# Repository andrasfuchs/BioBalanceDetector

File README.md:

Technically speaking Bio Balance Detector is a software and hardware combination (a data acquisition system - DAS) to detect, measure, display and analyze the electromagnetic energy field around living beings and indicate any potential health imbalance.  
  
These very weak, but measurable electromagnetic fields are the same what our doctors use while using an EEG (electroencephalogram) and ECG (electrocardiogram) devices. We use the information gathered there mainly to detect if we are sleeping, awake or alert, or if there is any problem with our heart's. My goal is to extend this phenomenon's measurements to our hands, or even our whole body.  
  
Technically I will need to connect an electromagnetic sensor matrix which is connected to a PC where the rendering would take place. It will look similar to a Wacom tablet, just like this:

Right now, with my [Mercury-16 prototype](https://github.com/andrasfuchs/BioBalanceDetector/wiki/Proto-%235---Mercury-16)  I reached a point where I have a working sensor matrix connected to a microcontroller. Every microcontroller is connected to 8 sensors and 1 emitter. The sensors detect electromagnetic fields, the emitters generate those fields. This part (1 microcontroller, 8 sensors, 1 emitter) is called the cell. These cells are daisy-chained and they all are connected to another microcontroller called the organizer. The cells digitize the analog signals (at 1kHz, 12bit) from the sensors (antennas) and forward them to the organizer. The organizer's job is to format the raw data and send it to the PC trough USB. The PC has a driver which further processes the data, and applies the filters if necessary. There are now WAV file writer, VTS file writer, FFT (Fast Fourier Transformation), averager and offsetter filters available. The driver is capable to work with [SciLab](http://www.scilab.org/) and [ParaView](https://www.paraview.org/), and it also has a very basic console application UI.  
  
You can browse the technical challenges I worked and I am working on on the [implementation wiki page](https://github.com/andrasfuchs/BioBalanceDetector/wiki/Implementation). Future plans include, but not limited to: fractal antenna design, analog low-pass Butterworth filters, Goertzel algorithm implementation on the cells, emitters, USB 3.0, Unity3D GUI and many more.  
  
I realize at this point that I need experienced, passionate people to more forward. I'm currently looking for people with the following expertise, so don't hesitate to contact me:  
* Hardware designer: PCB with [KiCad](https://www.kicad-pcb.org/), antenna and analog low pass filter design  
* Microcontroller firmware programmer: Atmel XMEGA programming with AVR C  
* PC driver developer: .NET, C#, signal processing and WebSockets  
* GUI: Unity3D, C# and WebSockets  
  
If you would like to get know the project more, check out the [wiki page](http://bit.ly/29OBsJ2) or contact me at <andras.fuchs@gmail.com>.

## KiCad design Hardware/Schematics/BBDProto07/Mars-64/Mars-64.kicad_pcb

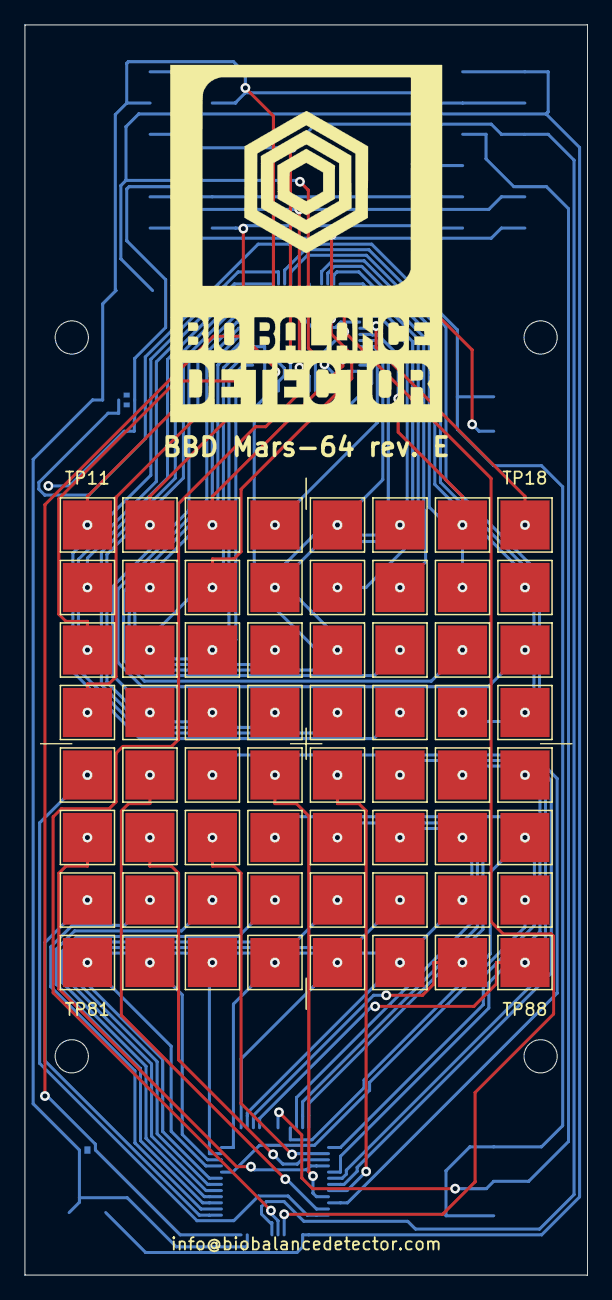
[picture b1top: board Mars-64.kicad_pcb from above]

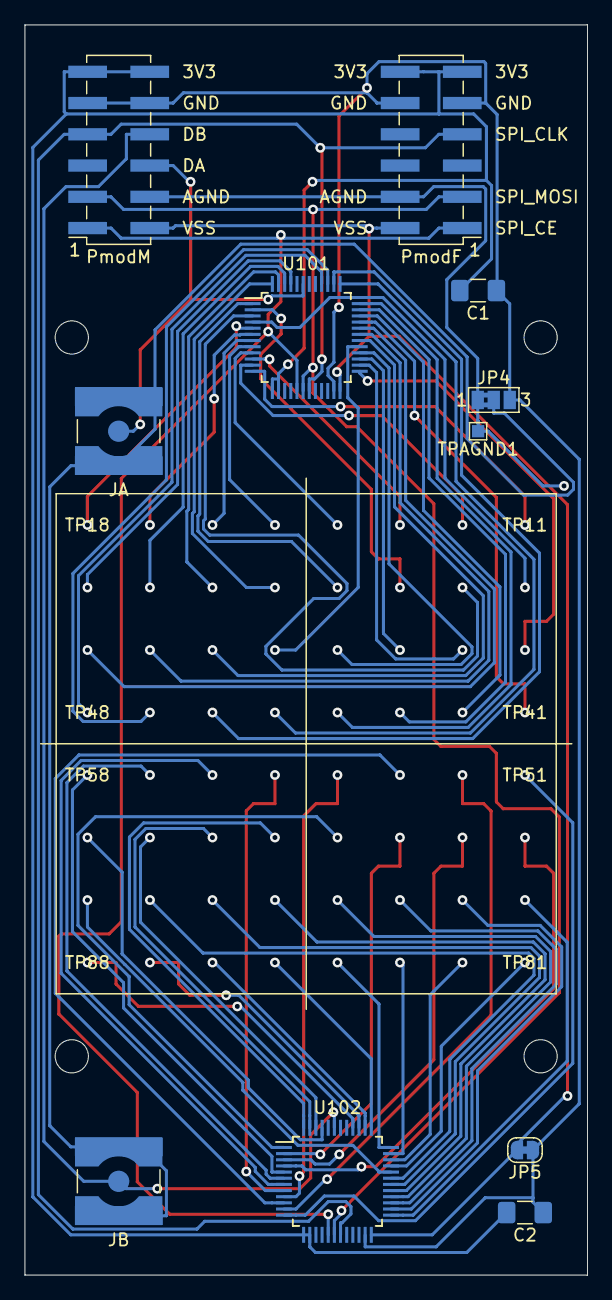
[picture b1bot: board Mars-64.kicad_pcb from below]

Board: 4 copper layers, 45.7 x 101.6 mm, 79 parts (11 on the bottom side), 74 nets.

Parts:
C1, C2: 100 nF; C_1206_3216Metric_Pad1.42x1.75mm_HandSolder
H1, H2, H3, H4: MountingHole; MountingHole_2.7mm_M2.5
JA: Conn_Coaxial; SMA_Amphenol_132134-10_Vertical
JB: Conn_Coaxial; SMA_Amphenol_132134-10_Vertical
JP4: Jumper_NC_Dual; SolderJumper-3_P1.3mm_Bridged2Bar12_Pad1.0x1.5mm_NumberLabe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
JP5: SolderJumper_2_Bridged; SolderJumper-2_P1.3mm_Bridged_RoundedPad1.0x1.5mm
PmodF: Conn_02x06_Top_Bottom; PinHeader_2x06_P2.54mm_Vertical_SMD_TopBottom
PmodM: Conn_02x06_Top_Bottom; PinHeader_2x06_P2.54mm_Vertical_SMD_TopBottom_Mirrored
TP101, TP102, TP103, TP104, TP105, TP106, TP107, TP108, TP109, TP110, TP111, TP112, TP113, TP114, TP115, TP116, TP117, TP118, TP119, TP120, TP121, TP122, TP123, TP124, TP125, TP126, TP127, TP128, TP129, TP130, TP131, TP132, TP201, TP202, TP203, TP204, TP205, TP206, TP207, TP208, TP209, TP210, TP211, TP212, TP213, TP214, TP215, TP216, TP217, TP218, TP219, TP220, TP221, TP222, TP223, TP224, TP225, TP226, TP227, TP228, TP229, TP230, TP231, TP232: TestPoint_Small; TestPoint_Pad_4.0x4.0mm
TPAGND1: TestPoint_Small; TestPoint_Pad_1.0x1.0mm
U101, U102: ADG731; TQFP-48_7x7mm_P0.5mm

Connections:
/AGND: JP4.1, PmodF.8, PmodM.8, TPAGND1.1
/DA: JA.1, PmodM.9, U101.43
/DB: JB.1, PmodM.10, U102.43
/SPI_CLK: PmodF.4, PmodM.4, U101.19, U102.19
/SPI_MOSI: PmodF.2, PmodM.2, U101.18, U102.18
/VCC3V3: C1.2, C2.2, PmodF.6, PmodF.12, PmodM.6, PmodM.12, U101.13, U101.14, U102.13, U102.14
/VSS: JP5.2, PmodF.7, PmodM.7, U101.24, U102.24
/~SPI_CE: PmodF.1, PmodM.1, U101.17, U102.17
GND: C1.1, C2.1, JP4.3, JP5.1, PmodF.5, PmodF.11, PmodM.5, PmodM.11, U101.23, U102.23
unnamed: JA.2, JB.2, JP4.2
unnamed: TP101.1, U101.12
unnamed: TP102.1, U101.11
unnamed: TP103.1, U101.10
unnamed: TP104.1, U101.9
unnamed: TP105.1, U101.8
unnamed: TP106.1, U101.7
unnamed: TP107.1, U101.6
unnamed: TP108.1, U101.5
unnamed: TP109.1, U101.4
unnamed: TP110.1, U101.3
unnamed: TP111.1, U101.2
unnamed: TP112.1, U101.1
unnamed: TP113.1, U101.48
unnamed: TP114.1, U101.47
unnamed: TP115.1, U101.46
unnamed: TP116.1, U101.45
unnamed: TP117.1, U101.25
unnamed: TP118.1, U101.26
unnamed: TP119.1, U101.27
unnamed: TP120.1, U101.28
unnamed: TP121.1, U101.29
unnamed: TP122.1, U101.30
unnamed: TP123.1, U101.31
unnamed: TP124.1, U101.32
unnamed: TP125.1, U101.33
unnamed: TP126.1, U101.34
unnamed: TP127.1, U101.35
unnamed: TP128.1, U101.36
unnamed: TP129.1, U101.37
unnamed: TP130.1, U101.38
unnamed: TP131.1, U101.39
unnamed: TP132.1, U101.40
unnamed: TP201.1, U102.12
unnamed: TP202.1, U102.11
unnamed: TP203.1, U102.10
unnamed: TP204.1, U102.9
unnamed: TP205.1, U102.8
unnamed: TP206.1, U102.7
unnamed: TP207.1, U102.6
unnamed: TP208.1, U102.5
unnamed: TP209.1, U102.4
unnamed: TP210.1, U102.3
unnamed: TP211.1, U102.2
unnamed: TP212.1, U102.1
unnamed: TP213.1, U102.48
unnamed: TP214.1, U102.47
unnamed: TP215.1, U102.46
unnamed: TP216.1, U102.45
unnamed: TP217.1, U102.25
unnamed: TP218.1, U102.26
unnamed: TP219.1, U102.27
unnamed: TP220.1, U102.28
unnamed: TP221.1, U102.29
unnamed: TP222.1, U102.30
unnamed: TP223.1, U102.31
unnamed: TP224.1, U102.32
unnamed: TP225.1, U102.33
unnamed: TP226.1, U102.34
unnamed: TP227.1, U102.35
unnamed: TP228.1, U102.36
unnamed: TP229.1, U102.37
unnamed: TP230.1, U102.38
unnamed: TP231.1, U102.39
unnamed: TP232.1, U102.40

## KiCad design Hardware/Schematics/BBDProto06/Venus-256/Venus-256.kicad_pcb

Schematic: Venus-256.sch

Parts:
JP101: VOUT1_JP; SolderJumper-2_P1.3mm_Bridged2Bar_Pad1.0x1.5mm
JP102: VOUT2_JP; SolderJumper-2_P1.3mm_Bridged2Bar_Pad1.0x1.5mm
TP101: VOUT3_TP; TestPoint_Pad_1.0x1.0mm
TP102: VOUT4_TP; TestPoint_Pad_1.0x1.0mm
U101: TPS22993; Texas_S-PWQFN-N20

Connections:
/CellMaster-01/VCC_MCU_P3V3: JP101.2; also elsewhere on the board
/CellMaster-02/VCC_MCU_P3V3: JP102.2; also elsewhere on the board
/RaspberryPiGPIOHeader/DC_POWER_3V3: U101.2, U101.4, U101.7, U101.8, U101.9, U101.10, U101.12, U101.14, U101.18; also elsewhere on the board
/RaspberryPiGPIOHeader/DC_POWER_5V0: U101.3; also elsewhere on the board
/RaspberryPiGPIOHeader/I2C_SCL1: U101.17; also elsewhere on the board
/RaspberryPiGPIOHeader/I2C_SDA1: U101.19; also elsewhere on the board
GND: U101.6, U101.13, U101.16, U101.20; also elsewhere on the board
unnamed: JP101.1, U101.5
unnamed: JP102.1, U101.1
unnamed: TP101.1, U101.15
unnamed: TP102.1, U101.11

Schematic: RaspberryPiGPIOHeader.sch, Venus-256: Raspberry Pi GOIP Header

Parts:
J201: RaspberryPi header; PinHeader_2x20_P2.54mm_Horizontal

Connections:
/CellMaster-01/SPI0_MISO: J201.21; also elsewhere on the board
/CellMaster-01/SPI0_MOSI: J201.19; also elsewhere on the board
/CellMaster-01/SPI0_SPCK: J201.23; also elsewhere on the board
/RaspberryPiGPIOHeader/DC_POWER_3V3: J201.1, J201.17; also elsewhere on the board
/RaspberryPiGPIOHeader/DC_POWER_5V0: J201.2, J201.4; also elsewhere on the board
/RaspberryPiGPIOHeader/I2C_SCL1: J201.5; also elsewhere on the board
/RaspberryPiGPIOHeader/I2C_SDA1: J201.3; also elsewhere on the board
GND: J201.6, J201.9, J201.14, J201.20, J201.25, J201.30, J201.34, J201.39; also elsewhere on the board

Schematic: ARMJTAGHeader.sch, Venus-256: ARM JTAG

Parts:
J301: ARM JTAG; PinHeader_2x10_P2.54mm_Horizontal
R301, R302, R303, R304: 0R; R_0603_1608Metric_Pad0.84x1.00mm_HandSolder

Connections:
/ARMJTAGHeader/SWCLK: R301.1; also elsewhere on the board
/ARMJTAGHeader/SWDIO: R303.2; also elsewhere on the board
/ARMJTAGHeader/TARGET_RESET: R302.1; also elsewhere on the board
/ARMJTAGHeader/TRACESWO: R304.2; also elsewhere on the board
/RaspberryPiGPIOHeader/DC_POWER_3V3: J301.1, J301.2; also elsewhere on the board
GND: J301.4, J301.6, J301.8, J301.10, J301.12, J301.14, J301.16, J301.18, J301.20; also elsewhere on the board
unnamed: J301.7, R303.1
unnamed: J301.9, R301.2
unnamed: J301.13, R304.1
unnamed: J301.15, R302.2

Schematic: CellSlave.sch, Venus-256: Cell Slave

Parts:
C401, C405, C407, C409, C411, C413, C416: 10uF; C_0603_1608Metric_Pad0.84x1.00mm_HandSolder
C402, C406, C408, C410, C412, C414, C415: 0.1uF; C_0603_1608Metric_Pad0.84x1.00mm_HandSolder
C403: 0.1uF,X8R; C_0603_1608Metric_Pad0.84x1.00mm_HandSolder
C404: 10uF,X5R; C_0603_1608Metric_Pad0.84x1.00mm_HandSolder
TP401: S01; TestPoint_Pad_1.0x1.0mm
TP402: S02; TestPoint_Pad_1.0x1.0mm
TP403: S03; TestPoint_Pad_1.0x1.0mm
TP404: S04; TestPoint_Pad_1.0x1.0mm
TP405: S05; TestPoint_Pad_1.0x1.0mm
TP406: S06; TestPoint_Pad_1.0x1.0mm
TP407: S07; TestPoint_Pad_1.0x1.0mm
TP408: S08; TestPoint_Pad_1.0x1.0mm
TP409: S09; TestPoint_Pad_1.0x1.0mm
TP410: S10; TestPoint_Pad_1.0x1.0mm
TP411: S11; TestPoint_Pad_1.0x1.0mm
TP412: S12; TestPoint_Pad_1.0x1.0mm
TP413: S13; TestPoint_Pad_1.0x1.0mm
TP414: S14; TestPoint_Pad_1.0x1.0mm
TP415: S15; TestPoint_Pad_1.0x1.0mm
TP416: S16; TestPoint_Pad_1.0x1.0mm
TP417: ADC_REF_OUT; TestPoint_Pad_1.0x1.0mm
U401: AD7616; LQFP-80_14x14mm_P0.65mm

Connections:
/CellMaster-01/ADC_BUSY0: U401.67; also elsewhere on the board
/CellMaster-01/ADC_CONVST0: U401.68; also elsewhere on the board
/CellMaster-01/ADC_RESET: U401.36; also elsewhere on the board
/CellMaster-01/DAC0: U401.1, U401.3, U401.8, U401.10, U401.11, U401.13, U401.18, U401.20, U401.21, U401.23, U401.25, U401.27, U401.74, U401.76, U401.78, U401.80; also elsewhere on the board
/CellMaster-01/SPI1_NPCS0: U401.63; also elsewhere on the board
/CellSlave-01A/SCLK: U401.55, U401.62; also elsewhere on the board
/CellSlave-01A/SDOA: U401.57; also elsewhere on the board
/RaspberryPiGPIOHeader/DC_POWER_3V3: C413.2, C414.2, U401.35, U401.40, U401.49; also elsewhere on the board
/RaspberryPiGPIOHeader/DC_POWER_5V0: C405.2, C406.1, C407.2, C408.2, C409.2, C410.2, C411.2, C412.2, U401.6, U401.15, U401.30, U401.71; also elsewhere on the board
GND: C401.2, C402.2, C403.2, C404.2, C405.1, C406.2, C407.1, C408.1, C409.1, C410.1, C411.1, C412.1, C413.1, C414.1, C415.2, C416.2, U401.5, U401.16, U401.29, U401.32, U401.34, U401.37, U401.38, U401.39, U401.41, U401.42, U401.43, U401.44, U401.45, U401.46, U401.47, U401.48, U401.50, U401.51, U401.53, U401.54, U401.58, U401.59, U401.60, U401.61, U401.64, U401.65, U401.66, U401.69, U401.72; also elsewhere on the board
unnamed: C401.1, C402.1, U401.70
unnamed: C403.1, TP417.1, U401.33
unnamed: C404.1, U401.31
unnamed: C415.1, C416.1, U401.52
unnamed: TP401.1, U401.73
unnamed: TP402.1, U401.75
unnamed: TP403.1, U401.77
unnamed: TP404.1, U401.79
unnamed: TP405.1, U401.9
unnamed: TP406.1, U401.7
unnamed: TP407.1, U401.4
unnamed: TP408.1, U401.2
unnamed: TP409.1, U401.19
unnamed: TP410.1, U401.17
unnamed: TP411.1, U401.14
unnamed: TP412.1, U401.12
unnamed: TP413.1, U401.28
unnamed: TP414.1, U401.26
unnamed: TP415.1, U401.24
unnamed: TP416.1, U401.22

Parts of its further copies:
C601, C605, C607, C609, C611, C613, C616, C701, C705, C707, C709, C711, C713, C716, C801, C805, C807, C809, C811, C813, C816, C1001, C1005, C1007, C1009, C1011, C1013, C1016: 10uF; C_0603_1608Metric_Pad0.84x1.00mm_HandSolder
C602, C606, C608, C610, C612, C614, C615, C702, C706, C708, C710, C712, C714, C715, C802, C806, C808, C810, C812, C814, C815, C1002, C1006, C1008, C1010, C1012, C1014, C1015: 0.1uF; C_0603_1608Metric_Pad0.84x1.00mm_HandSolder
C603, C703, C803, C1003: 0.1uF,X8R; C_0603_1608Metric_Pad0.84x1.00mm_HandSolder
C604, C704, C804, C1004: 10uF,X5R; C_0603_1608Metric_Pad0.84x1.00mm_HandSolder
TP601, TP701, TP801, TP1001: S01; TestPoint_Pad_1.0x1.0mm
TP602, TP702, TP802, TP1002: S02; TestPoint_Pad_1.0x1.0mm
TP603, TP703, TP803, TP1003: S03; TestPoint_Pad_1.0x1.0mm
TP604, TP704, TP804, TP1004: S04; TestPoint_Pad_1.0x1.0mm
TP605, TP705, TP805, TP1005: S05; TestPoint_Pad_1.0x1.0mm
TP606, TP706, TP806, TP1006: S06; TestPoint_Pad_1.0x1.0mm
TP607, TP707, TP807, TP1007: S07; TestPoint_Pad_1.0x1.0mm
TP608, TP708, TP808, TP1008: S08; TestPoint_Pad_1.0x1.0mm
TP609, TP709, TP809, TP1009: S09; TestPoint_Pad_1.0x1.0mm
TP610, TP710, TP810, TP1010: S10; TestPoint_Pad_1.0x1.0mm
TP611, TP711, TP811, TP1011: S11; TestPoint_Pad_1.0x1.0mm
TP612, TP712, TP812, TP1012: S12; TestPoint_Pad_1.0x1.0mm
TP613, TP713, TP813, TP1013: S13; TestPoint_Pad_1.0x1.0mm
TP614, TP714, TP814, TP1014: S14; TestPoint_Pad_1.0x1.0mm
TP615, TP715, TP815, TP1015: S15; TestPoint_Pad_1.0x1.0mm
TP616, TP716, TP816, TP1016: S16; TestPoint_Pad_1.0x1.0mm
TP617, TP717, TP817, TP1017: ADC_REF_OUT; TestPoint_Pad_1.0x1.0mm
U601, U701, U801, U1001: AD7616; LQFP-80_14x14mm_P0.65mm

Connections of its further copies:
/CellMaster-01/ADC_BUSY1: U601.67; also elsewhere on the board
/CellMaster-01/ADC_BUSY2: U701.67; also elsewhere on the board
/CellMaster-01/ADC_BUSY3: U801.67; also elsewhere on the board
/CellMaster-01/ADC_CONVST1: U601.68; also elsewhere on the board
/CellMaster-01/ADC_CONVST2: U701.68; also elsewhere on the board
/CellMaster-01/ADC_CONVST3: U801.68; also elsewhere on the board
/CellMaster-01/ADC_RESET: U601.36, U701.36, U801.36; also elsewhere on the board
/CellMaster-01/DAC0: U601.1, U601.3, U601.8, U601.10, U601.11, U601.13, U601.18, U601.20, U601.21, U601.23, U601.25, U601.27, U601.74, U601.76, U601.78, U601.80, U701.1, U701.3, U701.8, U701.10, U701.11, U701.13, U701.18, U701.20, U701.21, U701.23, U701.25, U701.27, U701.74, U701.76, U701.78, U701.80, U801.1, U801.3, U801.8, U801.10, U801.11, U801.13, U801.18, U801.20, U801.21, U801.23, U801.25, U801.27, U801.74, U801.76, U801.78, U801.80; also elsewhere on the board
/CellMaster-01/SPI1_NPCS1: U601.63; also elsewhere on the board
/CellMaster-01/SPI1_NPCS2: U701.63; also elsewhere on the board
/CellMaster-01/SPI1_NPCS3: U801.63; also elsewhere on the board
/CellMaster-02/ADC_BUSY0: U1001.67; also elsewhere on the board
/CellMaster-02/ADC_CONVST0: U1001.68; also elsewhere on the board
/CellMaster-02/ADC_RESET: U1001.36; also elsewhere on the board
/CellMaster-02/DAC0: U1001.1, U1001.3, U1001.8, U1001.10, U1001.11, U1001.13, U1001.18, U1001.20, U1001.21, U1001.23, U1001.25, U1001.27, U1001.74, U1001.76, U1001.78, U1001.80; also elsewhere on the board
/CellMaster-02/SPI1_NPCS0: U1001.63; also elsewhere on the board
/CellSlave-01A/SCLK: U601.55, U601.62, U701.55, U701.62, U801.55, U801.62; also elsewhere on the board
/CellSlave-01A/SDOA: U601.57, U701.57, U801.57; also elsewhere on the board
/CellSlave-02A/SCLK: U1001.62; also elsewhere on the board
/CellSlave-02A/SDI: U1001.55; also elsewhere on the board
/CellSlave-02A/SDOA: U1001.57; also elsewhere on the board
/RaspberryPiGPIOHeader/DC_POWER_3V3: C613.2, C614.2, C713.2, C714.2, C813.2, C814.2, C1013.2, C1014.2, U601.35, U601.40, U601.49, U701.35, U701.40, U701.49, U801.35, U801.40, U801.49, U1001.35, U1001.40, U1001.49; also elsewhere on the board
/RaspberryPiGPIOHeader/DC_POWER_5V0: C605.2, C606.1, C607.2, C608.2, C609.2, C610.2, C611.2, C612.2, C705.2, C706.1, C707.2, C708.2, C709.2, C710.2, C711.2, C712.2, C805.2, C806.1, C807.2, C808.2, C809.2, C810.2, C811.2, C812.2, C1005.2, C1006.1, C1007.2, C1008.2, C1009.2, C1010.2, C1011.2, C1012.2, U601.6, U601.15, U601.30, U601.71, U701.6, U701.15, U701.30, U701.71, U801.6, U801.15, U801.30, U801.71, U1001.6, U1001.15, U1001.30, U1001.71; also elsewhere on the board
GND: C601.2, C602.2, C603.2, C604.2, C605.1, C606.2, C607.1, C608.1, C609.1, C610.1, C611.1, C612.1, C613.1, C614.1, C615.2, C616.2, C701.2, C702.2, C703.2, C704.2, C705.1, C706.2, C707.1, C708.1, C709.1, C710.1, C711.1, C712.1, C713.1, C714.1, C715.2, C716.2, C801.2, C802.2, C803.2, C804.2, C805.1, C806.2, C807.1, C808.1, C809.1, C810.1, C811.1, C812.1, C813.1, C814.1, C815.2, C816.2, C1001.2, C1002.2, C1003.2, C1004.2, C1005.1, C1006.2, C1007.1, C1008.1, C1009.1, C1010.1, C1011.1, C1012.1, C1013.1, C1014.1, C1015.2, C1016.2, U601.5, U601.16, U601.29, U601.32, U601.34, U601.37, U601.38, U601.39, U601.41, U601.42, U601.43, U601.44, U601.45, U601.46, U601.47, U601.48, U601.50, U601.51, U601.53, U601.54, U601.58, U601.59, U601.60, U601.61, U601.64, U601.65, U601.66, U601.69, U601.72, U701.5, U701.16, U701.29, U701.32, U701.34, U701.37, U701.38, U701.39, U701.41, U701.42, U701.43, U701.44, U701.45, U701.46, U701.47, U701.48, U701.50, U701.51, U701.53, U701.54, U701.58, U701.59, U701.60, U701.61, U701.64, U701.65, U701.66, U701.69, U701.72, U801.5, U801.16, U801.29, U801.32, U801.34, U801.37, U801.38, U801.39, U801.41, U801.42, U801.43, U801.44, U801.45, U801.46, U801.47, U801.48, U801.50, U801.51, U801.53, U801.54, U801.58, U801.59, U801.60, U801.61, U801.64, U801.65, U801.66, U801.69, U801.72, U1001.5, U1001.16, U1001.29, U1001.32, U1001.34, U1001.37, U1001.38, U1001.39, U1001.41, U1001.42, U1001.43, U1001.44, U1001.45, U1001.46, U1001.47, U1001.48, U1001.50, U1001.51, U1001.53, U1001.54, U1001.58, U1001.59, U1001.60, U1001.61, U1001.64, U1001.65, U1001.66, U1001.69, U1001.72; also elsewhere on the board
unnamed: C601.1, C602.1, U601.70
unnamed: C603.1, TP617.1, U601.33
unnamed: C604.1, U601.31
unnamed: C615.1, C616.1, U601.52
unnamed: C701.1, C702.1, U701.70
unnamed: C703.1, TP717.1, U701.33
unnamed: C704.1, U701.31
unnamed: C715.1, C716.1, U701.52
unnamed: C801.1, C802.1, U801.70
unnamed: C803.1, TP817.1, U801.33
unnamed: C804.1, U801.31
unnamed: C815.1, C816.1, U801.52
unnamed: C1001.1, C1002.1, U1001.70
unnamed: C1003.1, TP1017.1, U1001.33
unnamed: C1004.1, U1001.31
unnamed: C1015.1, C1016.1, U1001.52
unnamed: TP601.1, U601.73
unnamed: TP602.1, U601.75
unnamed: TP603.1, U601.77
unnamed: TP604.1, U601.79
unnamed: TP605.1, U601.9
unnamed: TP606.1, U601.7
unnamed: TP607.1, U601.4
unnamed: TP608.1, U601.2
unnamed: TP609.1, U601.19
unnamed: TP610.1, U601.17
unnamed: TP611.1, U601.14
unnamed: TP612.1, U601.12
unnamed: TP613.1, U601.28
unnamed: TP614.1, U601.26
unnamed: TP615.1, U601.24
unnamed: TP616.1, U601.22
unnamed: TP701.1, U701.73
unnamed: TP702.1, U701.75
unnamed: TP703.1, U701.77
unnamed: TP704.1, U701.79
unnamed: TP705.1, U701.9
unnamed: TP706.1, U701.7
unnamed: TP707.1, U701.4
unnamed: TP708.1, U701.2
unnamed: TP709.1, U701.19
unnamed: TP710.1, U701.17
unnamed: TP711.1, U701.14
unnamed: TP712.1, U701.12
unnamed: TP713.1, U701.28
unnamed: TP714.1, U701.26
unnamed: TP715.1, U701.24
unnamed: TP716.1, U701.22
unnamed: TP801.1, U801.73
unnamed: TP802.1, U801.75
unnamed: TP803.1, U801.77
unnamed: TP804.1, U801.79
unnamed: TP805.1, U801.9
unnamed: TP806.1, U801.7
unnamed: TP807.1, U801.4
unnamed: TP808.1, U801.2
unnamed: TP809.1, U801.19
unnamed: TP810.1, U801.17
unnamed: TP811.1, U801.14
unnamed: TP812.1, U801.12
unnamed: TP813.1, U801.28
unnamed: TP814.1, U801.26
unnamed: TP815.1, U801.24
unnamed: TP816.1, U801.22
unnamed: TP1001.1, U1001.73
unnamed: TP1002.1, U1001.75
unnamed: TP1003.1, U1001.77
unnamed: TP1004.1, U1001.79
unnamed: TP1005.1, U1001.9
unnamed: TP1006.1, U1001.7
unnamed: TP1007.1, U1001.4
unnamed: TP1008.1, U1001.2
unnamed: TP1009.1, U1001.19
unnamed: TP1010.1, U1001.17
unnamed: TP1011.1, U1001.14
unnamed: TP1012.1, U1001.12
unnamed: TP1013.1, U1001.28
unnamed: TP1014.1, U1001.26
unnamed: TP1015.1, U1001.24
unnamed: TP1016.1, U1001.22

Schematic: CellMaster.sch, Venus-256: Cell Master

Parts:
C501: 10uF; C_0603_1608Metric_Pad0.84x1.00mm_HandSolder
C502, C503, C504, C506, C507, C508, C509, C510, C511, C512, C513, C514, C515, C516: 100nF; C_0603_1608Metric_Pad0.84x1.00mm_HandSolder
C505: 10pF; C_0603_1608Metric_Pad0.84x1.00mm_HandSolder
D501: LED_ARGB; LED_RGB_1210
JP501: GPAD_JP; SolderJumper-3_P1.3mm_Open_Pad1.0x1.5mm
L501: L; L_0603_1608Metric_Pad0.84x1.00mm_HandSolder
R501: 5.62K; R_0603_1608Metric_Pad0.84x1.00mm_HandSolder
TP501: AFE0_AD0; TestPoint_Pad_1.0x1.0mm
TP502: AFE0_AD1; TestPoint_Pad_1.0x1.0mm
TP503: ADVREF; TestPoint_Pad_1.0x1.0mm
TP504: GPAD; TestPoint_Pad_1.0x1.0mm
U501: ATSAME70Q21A-AN; LQFP-144_20x20mm_P0.5mm

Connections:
/ARMJTAGHeader/SWCLK: U501.89 (PB7/SWCLK/TCK); also elsewhere on the board
/ARMJTAGHeader/SWDIO: U501.79 (PB6/SWDIO/TMS); also elsewhere on the board
/ARMJTAGHeader/TARGET_RESET: U501.83 (NRST); also elsewhere on the board
/ARMJTAGHeader/TRACESWO: U501.109 (PB5/TDO/TRACESWO/WKUP13); also elsewhere on the board
/CellMaster-01/ADC_BUSY0: U501.46 (PA23); also elsewhere on the board
/CellMaster-01/ADC_BUSY1: U501.56 (PA24); also elsewhere on the board
/CellMaster-01/ADC_BUSY2: U501.59 (PA25); also elsewhere on the board
/CellMaster-01/ADC_BUSY3: U501.62 (PA26); also elsewhere on the board
/CellMaster-01/ADC_CONVST0: U501.4 (PE0/AFE1_AD11); also elsewhere on the board
/CellMaster-01/ADC_CONVST1: U501.6 (PE1); also elsewhere on the board
/CellMaster-01/ADC_CONVST2: U501.7 (PE2); also elsewhere on the board
/CellMaster-01/ADC_CONVST3: U501.10 (PE3/AFE1_AD10); also elsewhere on the board
/CellMaster-01/ADC_RESET: U501.70 (PA27); also elsewhere on the board
/CellMaster-01/DAC0: U501.20 (PB1/AFE1_AD0/RTCOUT1), U501.144 (PB13/DAC0); also elsewhere on the board
/CellMaster-01/SPI0_MISO: U501.65 (SPI0_MISO/PD20); also elsewhere on the board
/CellMaster-01/SPI0_MOSI: U501.63 (SPI0_MOSI/PD21); also elsewhere on the board
/CellMaster-01/SPI0_SPCK: U501.60 (SPI0_SPCK/PD22); also elsewhere on the board
/CellMaster-01/SPI1_NPCS0: U501.133 (SPI1_NPCS0/PC25); also elsewhere on the board
/CellMaster-01/SPI1_NPCS1: U501.76 (SPI1_NPCS1/PC28); also elsewhere on the board
/CellMaster-01/SPI1_NPCS2: U501.16 (SPI1_NPCS2/AFE1_AD4/PC29); also elsewhere on the board
/CellMaster-01/SPI1_NPCS3: U501.15 (SPI1_NPCS3/AFE1_AD5/PC30); also elsewhere on the board
/CellMaster-01/VCC_MCU_P3V3: C501.1, C503.1, C504.1, C506.1, C507.1, C508.1, C509.1, C510.1, C511.1, C512.1, C513.1, C514.1, C515.1, C516.1, L501.2, U501.5 (VDDIN), U501.29 (VDDCORE), U501.30 (VDDIO), U501.33 (VDDCORE), U501.43 (VDDIO), U501.50 (VDDCORE), U501.72 (VDDIO), U501.80 (VDDIO), U501.81 (VDDCORE), U501.96 (VDDIO), U501.107 (VDDCORE), U501.134 (VDDUTMII), U501.143 (VDDPLLUSB); also elsewhere on the board
/CellSlave-01A/SCLK: U501.12 (SPI1_MOSI/AFE1_AD8/PC27), U501.130 (SPI1_SPCK/PC24); also elsewhere on the board
/CellSlave-01A/SDOA: U501.13 (SPI1_MISO/AFE1_AD7/PC26); also elsewhere on the board
GND: C501.2, C502.2, C503.2, C504.2, C505.2, C506.2, C507.2, C508.2, C509.2, C510.2, C511.2, C512.2, C513.2, C514.2, C515.2, C516.2, JP501.3, R501.2, U501.8 (VREFN), U501.44 (GND), U501.61 (GND), U501.95 (GND), U501.115 (GND), U501.135 (GND), U501.138 (GND); also elsewhere on the board
unnamed: C502.1, L501.1, TP503.1, U501.9 (VREFP)
unnamed: C505.1, R501.1, U501.140 (VBG)
unnamed: D501.1, U501.51 (PA14/WKUP8/PIODCEN1)
unnamed: D501.2, U501.42 (PA13/PIODC7)
unnamed: D501.3, U501.68 (PA12/PIODC6)
unnamed: D501.4, U501.64 (PA11/WKUP7/PIODC5)
unnamed: JP501.1, U501.1 (SPI1_NPCS1/DAC1/PD0)
unnamed: JP501.2, TP504.1
unnamed: TP501.1, U501.34 (UTXD3/AFE0_AD0/PD30)
unnamed: TP502.1, U501.32 (PA21/AFE0_AD1/PIODCEN2)

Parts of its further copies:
C901: 10uF; C_0603_1608Metric_Pad0.84x1.00mm_HandSolder
C902, C903, C904, C906, C907, C908, C909, C910, C911, C912, C913, C914, C915, C916: 100nF; C_0603_1608Metric_Pad0.84x1.00mm_HandSolder
C905: 10pF; C_0603_1608Metric_Pad0.84x1.00mm_HandSolder
D901: LED_ARGB; LED_RGB_1210
JP901: GPAD_JP; SolderJumper-3_P1.3mm_Open_Pad1.0x1.5mm
L901: L; L_0603_1608Metric_Pad0.84x1.00mm_HandSolder
R901: 5.62K; R_0603_1608Metric_Pad0.84x1.00mm_HandSolder
TP901: AFE0_AD0; TestPoint_Pad_1.0x1.0mm
TP902: AFE0_AD1; TestPoint_Pad_1.0x1.0mm
TP903: ADVREF; TestPoint_Pad_1.0x1.0mm
TP904: GPAD; TestPoint_Pad_1.0x1.0mm
U901: ATSAME70Q21A-AN; LQFP-144_20x20mm_P0.5mm

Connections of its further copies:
/ARMJTAGHeader/SWCLK: U901.89 (PB7/SWCLK/TCK); also elsewhere on the board
/ARMJTAGHeader/SWDIO: U901.79 (PB6/SWDIO/TMS); also elsewhere on the board
/ARMJTAGHeader/TARGET_RESET: U901.83 (NRST); also elsewhere on the board
/ARMJTAGHeader/TRACESWO: U901.109 (PB5/TDO/TRACESWO/WKUP13); also elsewhere on the board
/CellMaster-01/SPI0_MISO: U901.65 (SPI0_MISO/PD20); also elsewhere on the board
/CellMaster-01/SPI0_MOSI: U901.63 (SPI0_MOSI/PD21); also elsewhere on the board
/CellMaster-01/SPI0_SPCK: U901.60 (SPI0_SPCK/PD22); also elsewhere on the board
/CellMaster-02/ADC_BUSY0: U901.46 (PA23); also elsewhere on the board
/CellMaster-02/ADC_CONVST0: U901.4 (PE0/AFE1_AD11); also elsewhere on the board
/CellMaster-02/ADC_RESET: U901.70 (PA27); also elsewhere on the board
/CellMaster-02/DAC0: U901.20 (PB1/AFE1_AD0/RTCOUT1), U901.144 (PB13/DAC0); also elsewhere on the board
/CellMaster-02/SPI1_NPCS0: U901.133 (SPI1_NPCS0/PC25); also elsewhere on the board
/CellMaster-02/VCC_MCU_P3V3: C901.1, C903.1, C904.1, C906.1, C907.1, C908.1, C909.1, C910.1, C911.1, C912.1, C913.1, C914.1, C915.1, C916.1, L901.2, U901.5 (VDDIN), U901.29 (VDDCORE), U901.30 (VDDIO), U901.33 (VDDCORE), U901.43 (VDDIO), U901.50 (VDDCORE), U901.72 (VDDIO), U901.80 (VDDIO), U901.81 (VDDCORE), U901.96 (VDDIO), U901.107 (VDDCORE), U901.134 (VDDUTMII), U901.143 (VDDPLLUSB); also elsewhere on the board
/CellSlave-02A/SCLK: U901.130 (SPI1_SPCK/PC24); also elsewhere on the board
/CellSlave-02A/SDI: U901.12 (SPI1_MOSI/AFE1_AD8/PC27); also elsewhere on the board
/CellSlave-02A/SDOA: U901.13 (SPI1_MISO/AFE1_AD7/PC26); also elsewhere on the board
GND: C901.2, C902.2, C903.2, C904.2, C905.2, C906.2, C907.2, C908.2, C909.2, C910.2, C911.2, C912.2, C913.2, C914.2, C915.2, C916.2, JP901.3, R901.2, U901.8 (VREFN), U901.44 (GND), U901.61 (GND), U901.95 (GND), U901.115 (GND), U901.135 (GND), U901.138 (GND); also elsewhere on the board
unnamed: C902.1, L901.1, TP903.1, U901.9 (VREFP)
unnamed: C905.1, R901.1, U901.140 (VBG)
unnamed: D901.1, U901.51 (PA14/WKUP8/PIODCEN1)
unnamed: D901.2, U901.42 (PA13/PIODC7)
unnamed: D901.3, U901.68 (PA12/PIODC6)
unnamed: D901.4, U901.64 (PA11/WKUP7/PIODC5)
unnamed: JP901.1, U901.1 (SPI1_NPCS1/DAC1/PD0)
unnamed: JP901.2, TP904.1
unnamed: TP901.1, U901.34 (UTXD3/AFE0_AD0/PD30)
unnamed: TP902.1, U901.32 (PA21/AFE0_AD1/PIODCEN2)

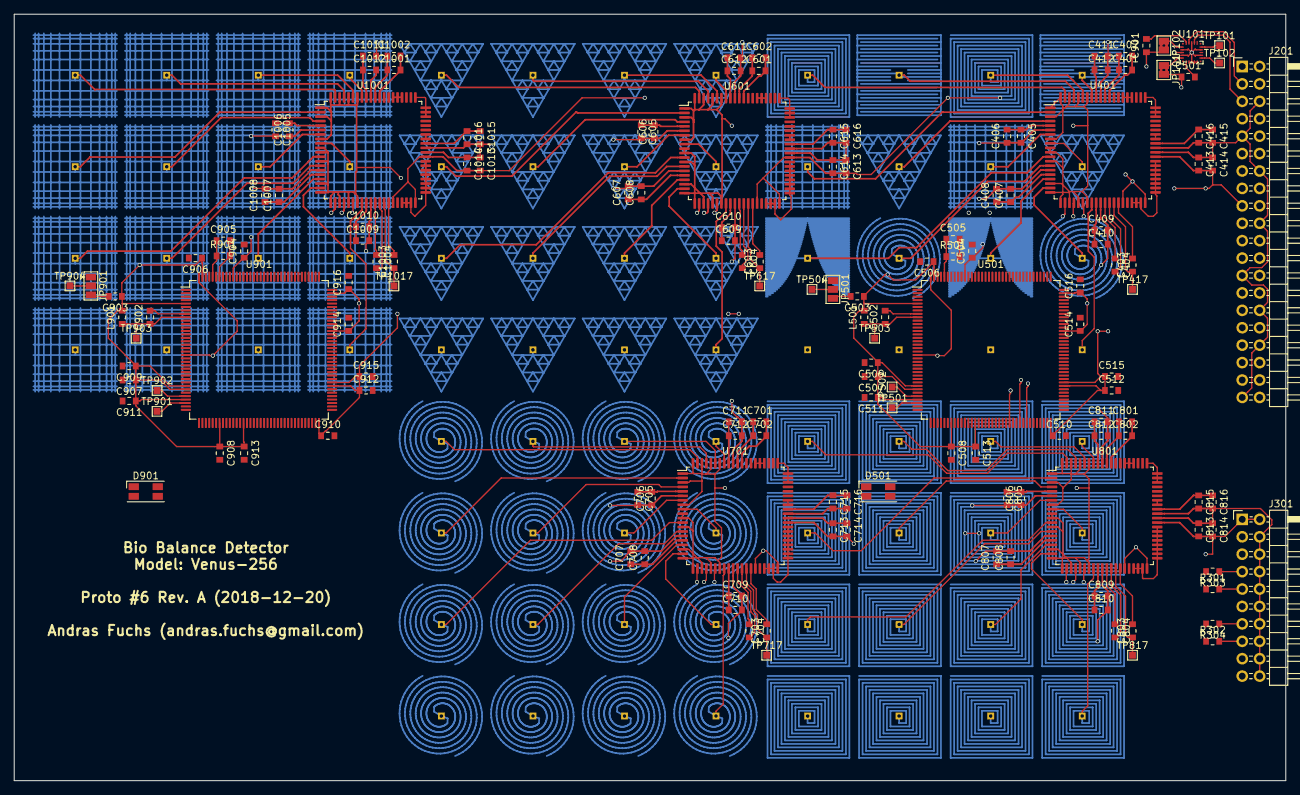
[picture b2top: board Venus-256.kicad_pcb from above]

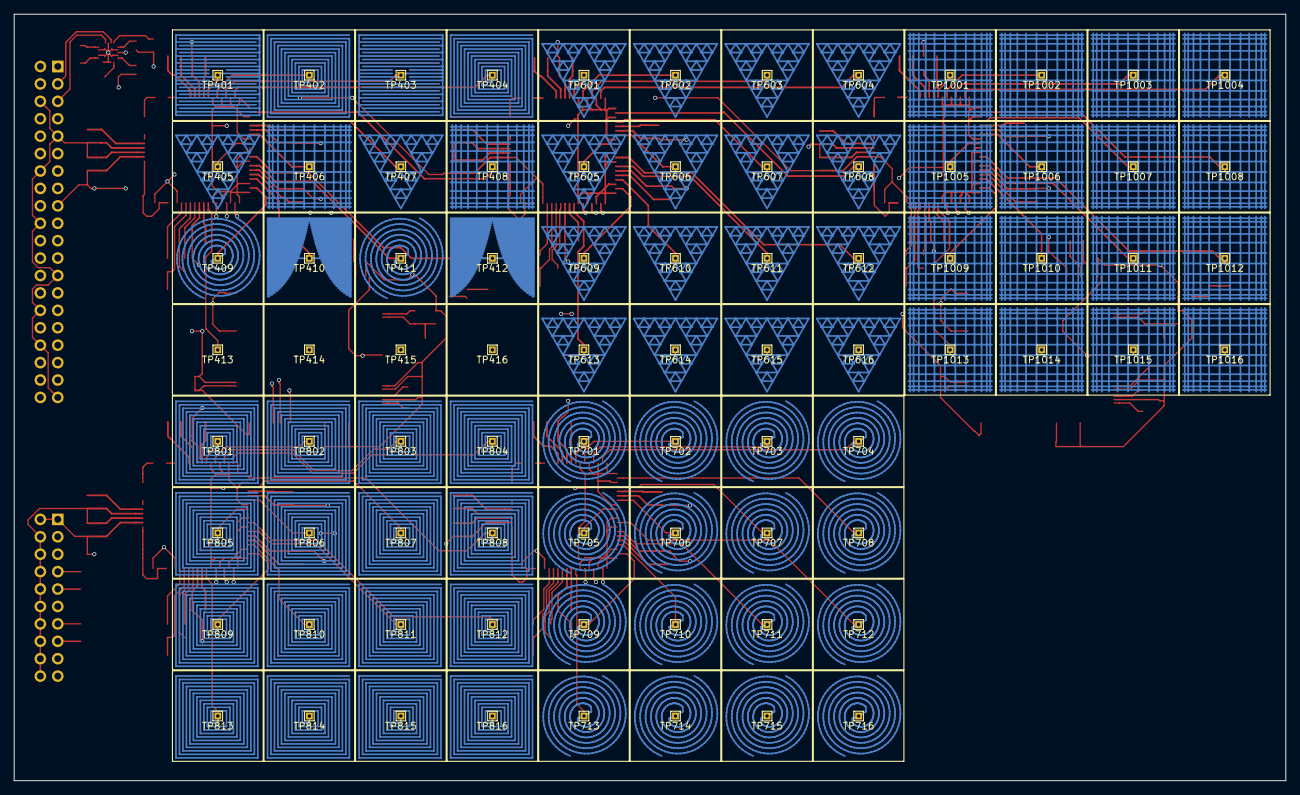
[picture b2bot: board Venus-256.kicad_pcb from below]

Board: 4 copper layers, 185.4 x 111.8 mm, 231 parts (80 on the bottom side), 166 nets.

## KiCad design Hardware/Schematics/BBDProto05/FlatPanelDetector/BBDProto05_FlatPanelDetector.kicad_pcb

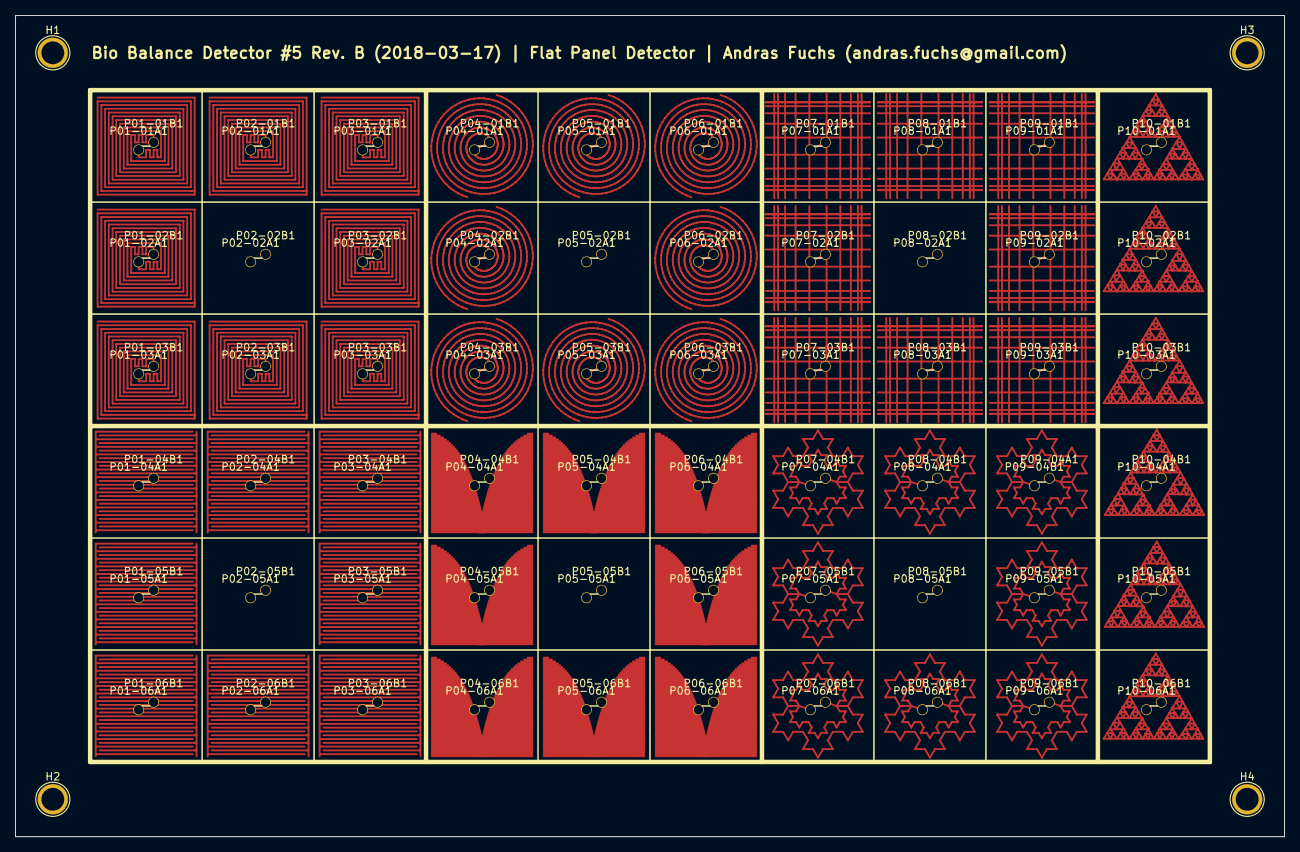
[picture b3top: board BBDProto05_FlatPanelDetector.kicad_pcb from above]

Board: 2 copper layers, 170.0 x 110.0 mm, 124 parts (0 on the bottom side), 60 nets.

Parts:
H1, H2, H3, H4: VIA_06MM; 1pin
P01-01A1, P01-01B1, P01-02A1, P01-02B1, P01-03A1, P01-03B1, P01-04A1, P01-04B1, P01-05A1, P01-05B1, P01-06A1, P01-06B1, P02-01A1, P02-01B1, P02-02A1, P02-02B1, P02-03A1, P02-03B1, P02-04A1, P02-04B1, P02-05A1, P02-05B1, P02-06A1, P02-06B1, P03-01A1, P03-01B1, P03-02A1, P03-02B1, P03-03A1, P03-03B1, P03-04A1, P03-04B1, P03-05A1, P03-05B1, P03-06A1, P03-06B1, P04-01A1, P04-01B1, P04-02A1, P04-02B1, P04-03A1, P04-03B1, P04-04A1, P04-04B1, P04-05A1, P04-05B1, P04-06A1, P04-06B1, P05-01A1, P05-01B1, P05-02A1, P05-02B1, P05-03A1, P05-03B1, P05-04A1, P05-04B1, P05-05A1, P05-05B1, P05-06A1, P05-06B1, P06-01A1, P06-01B1, P06-02A1, P06-02B1, P06-03A1, P06-03B1, P06-04A1, P06-04B1, P06-05A1, P06-05B1, P06-06A1, P06-06B1, P07-01A1, P07-01B1, P07-02A1, P07-02B1, P07-03A1, P07-03B1, P07-04A1, P07-04B1, P07-05A1, P07-05B1, P07-06A1, P07-06B1, P08-01A1, P08-01B1, P08-02A1, P08-02B1, P08-03A1, P08-03B1, P08-04A1, P08-04B1, P08-05A1, P08-05B1, P08-06A1, P08-06B1, P09-01A1, P09-01B1, P09-02A1, P09-02B1, P09-03A1, P09-03B1, P09-04A1, P09-04B1, P09-05A1, P09-05B1, P09-06A1, P09-06B1, P10-01A1, P10-01B1, P10-02A1, P10-02B1, P10-03A1, P10-03B1, P10-04A1, P10-04B1, P10-05A1, P10-05B1, P10-06A1, P10-06B1: VIA_06MM; SolderWirePad_single_0-4mmDrill

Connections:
unnamed: P01-01A1.1, P01-01B1.1
unnamed: P01-02A1.e1, P01-02B1.1
unnamed: P01-03A1.1, P01-03B1.1
unnamed: P01-04A1.1, P01-04B1.1
unnamed: P01-05A1.1, P01-05B1.1
unnamed: P01-06A1.1, P01-06B1.1
unnamed: P02-01A1.1, P02-01B1.1
unnamed: P02-02A1.1, P02-02B1.1
unnamed: P02-03A1.1, P02-03B1.1
unnamed: P02-04A1.1, P02-04B1.1
unnamed: P02-05A1.1, P02-05B1.1
unnamed: P02-06A1.1, P02-06B1.1
unnamed: P03-01A1.1, P03-01B1.1
unnamed: P03-02A1.1, P03-02B1.1
unnamed: P03-03A1.1, P03-03B1.1
unnamed: P03-04A1.1, P03-04B1.1
unnamed: P03-05A1.1, P03-05B1.1
unnamed: P03-06A1.1, P03-06B1.1
unnamed: P04-01A1.1, P04-01B1.1
unnamed: P04-02A1.1, P04-02B1.1
unnamed: P04-03A1.1, P04-03B1.1
unnamed: P04-04A1.1, P04-04B1.1
unnamed: P04-05A1.1, P04-05B1.1
unnamed: P04-06A1.1, P04-06B1.1
unnamed: P05-01A1.1, P05-01B1.1
unnamed: P05-02A1.1, P05-02B1.1
unnamed: P05-03A1.1, P05-03B1.1
unnamed: P05-04A1.1, P05-04B1.1
unnamed: P05-05A1.1, P05-05B1.1
unnamed: P05-06A1.1, P05-06B1.1
unnamed: P06-01A1.1, P06-01B1.1
unnamed: P06-02A1.1, P06-02B1.1
unnamed: P06-03A1.1, P06-03B1.1
unnamed: P06-04A1.1, P06-04B1.1
unnamed: P06-05A1.1, P06-05B1.1
unnamed: P06-06A1.1, P06-06B1.1
unnamed: P07-01A1.1, P07-01B1.1
unnamed: P07-02A1.1, P07-02B1.1
unnamed: P07-03A1.1, P07-03B1.1
unnamed: P07-04A1.1, P07-04B1.1
unnamed: P07-05A1.1, P07-05B1.1
unnamed: P07-06A1.1, P07-06B1.1
unnamed: P08-01A1.1, P08-01B1.1
unnamed: P08-02A1.1, P08-02B1.1
unnamed: P08-03A1.1, P08-03B1.1
unnamed: P08-04A1.1, P08-04B1.1
unnamed: P08-05A1.1, P08-05B1.1
unnamed: P08-06A1.1, P08-06B1.1
unnamed: P09-01A1.1, P09-01B1.1
unnamed: P09-02A1.1, P09-02B1.1
unnamed: P09-03A1.1, P09-03B1.1
unnamed: P09-04A1.1, P09-04B1.1
unnamed: P09-05A1.1, P09-05B1.1
unnamed: P09-06A1.1, P09-06B1.1
unnamed: P10-01A1.1, P10-01B1.1
unnamed: P10-02A1.1, P10-02B1.1
unnamed: P10-03A1.1, P10-03B1.1
unnamed: P10-04A1.1, P10-04B1.1
unnamed: P10-05A1.1, P10-05B1.1
unnamed: P10-06A1.1, P10-06B1.1
